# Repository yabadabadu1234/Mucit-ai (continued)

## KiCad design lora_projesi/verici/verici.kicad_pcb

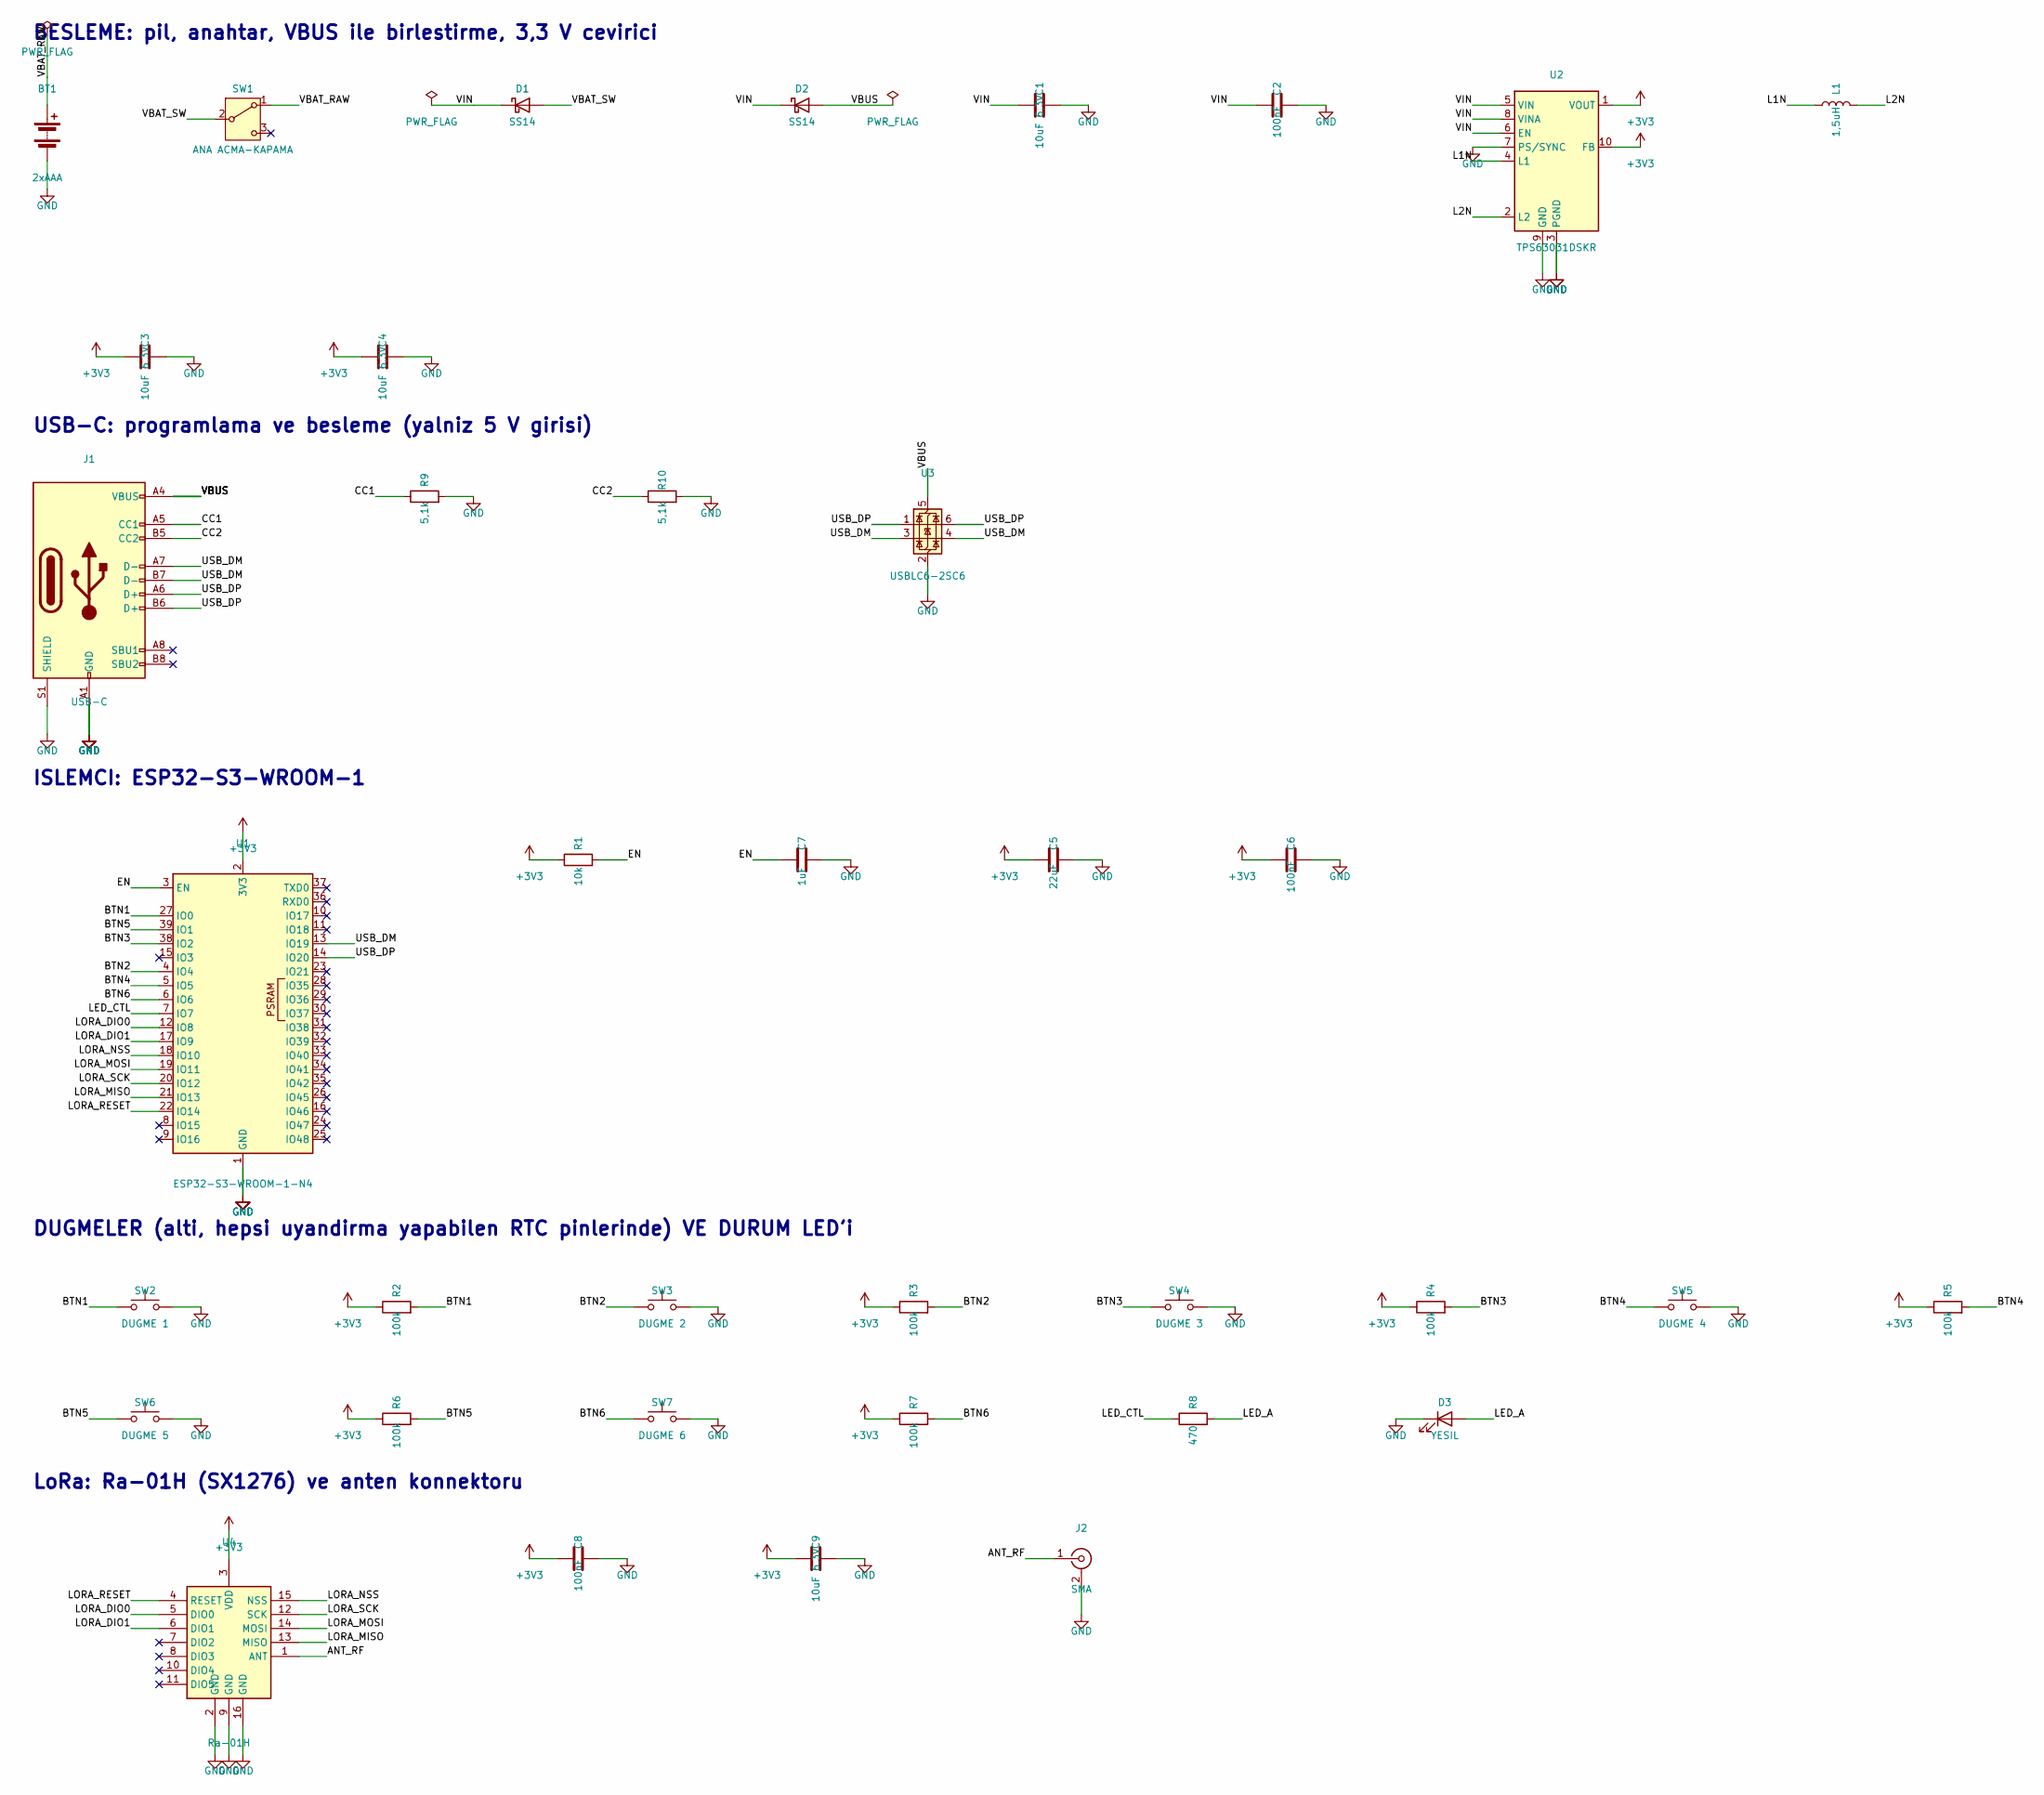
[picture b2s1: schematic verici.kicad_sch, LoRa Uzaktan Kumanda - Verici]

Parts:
BT1: 2xAAA; BatteryHolder_Keystone_2468_2xAAA; MPN Keystone 2468
C1, C3, C4, C9: 10uF 6,3V; C_0603_1608Metric
C2, C6, C8: 100nF; C_0603_1608Metric
C5: 22uF; C_0805_2012Metric
C7: 1uF; C_0603_1608Metric
D1, D2: SS14; D_SMA; MPN SS14
D3: YESIL; LED_0603_1608Metric
J1: USB-C; USB_C_Receptacle_GCT_USB4105-xx-A_16P_TopMnt_Horizontal; MPN GCT USB4105-GF-A
J2: SMA; SMA_Amphenol_132289_EdgeMount; MPN Amphenol 132289 (kenar SMA)
L1: 1,5uH; L_Cenker_CKCS3015; MPN 1,5uH 3x3mm (Coilcraft LPS3015-152 esde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
R1: 10k; R_0603_1608Metric
R2, R3, R4, R5, R6, R7: 100k; R_0603_1608Metric
R8: 470; R_0603_1608Metric
R9, R10: 5,1k; R_0603_1608Metric
SW1: ANA ACMA-KAPAMA; SW_SPDT_PCM12; MPN MSK12C02 (kayar anahtar)
SW2: DUGME 1; SW_SPST_TL3342
SW3: DUGME 2; SW_SPST_TL3342
SW4: DUGME 3; SW_SPST_TL3342
SW5: DUGME 4; SW_SPST_TL3342
SW6: DUGME 5; SW_SPST_TL3342
SW7: DUGME 6; SW_SPST_TL3342
U1: ESP32-S3-WROOM-1-N4; ESP32-S3-WROOM-1; MPN ESP32-S3-WROOM-1-N4
U2: TPS63031DSKR; WSON-10-1EP_2.5x2.5mm_P0.5mm_EP1.2x2mm; MPN TPS63031DSKR
U3: USBLC6-2SC6; SOT-23-6; MPN USBLC6-2SC6
U4: Ra-01H; MPN Ai-Thinker Ra-01H (LCSC C503593)

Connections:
+3V3: C3.1, C4.1, C5.1, C6.1, C8.1, C9.1, R1.1, R2.1, R3.1, R4.1, R5.1, R6.1, R7.1, U1.2 (3V3), U2.1 (VOUT), U2.10 (FB), U4.3 (VDD)
ANT_RF: J2.1 (In), U4.1 (ANT)
BTN1: R2.2, SW2.1, U1.27 (IO0)
BTN2: R3.2, SW3.1, U1.4 (IO4)
BTN3: R4.2, SW4.1, U1.38 (IO2)
BTN4: R5.2, SW5.1, U1.5 (IO5)
BTN5: R6.2, SW6.1, U1.39 (IO1)
BTN6: R7.2, SW7.1, U1.6 (IO6)
CC1: J1.A5 (CC1), R9.1
CC2: J1.B5 (CC2), R10.1
EN: C7.1, R1.2, U1.3 (EN)
GND: BT1.2 (-), C1.2, C2.2, C3.2, C4.2, C5.2, C6.2, C7.2, C8.2, C9.2, D3.1 (K), J1.A1 (GND), J1.A12 (GND), J1.B1 (GND), J1.B12 (GND), J1.S1 (SHIELD), J2.2 (Ext), R9.2, R10.2, SW2.2, SW3.2, SW4.2, SW5.2, SW6.2, SW7.2, U1.1 (GND), U1.40 (GND), U1.41 (GND), U2.3 (PGND), U2.7 (PS/SYNC), U2.9 (GND), U2.11 (PGND), U3.2 (GND), U4.2 (GND), U4.9 (GND), U4.16 (GND)
L1N: L1.1, U2.4 (L1)
L2N: L1.2, U2.2 (L2)
LED_A: D3.2 (A), R8.2
LED_CTL: R8.1, U1.7 (IO7)
LORA_DIO0: U1.12 (IO8), U4.5 (DIO0)
LORA_DIO1: U1.17 (IO9), U4.6 (DIO1)
LORA_MISO: U1.21 (IO13), U4.13 (MISO)
LORA_MOSI: U1.19 (IO11), U4.14 (MOSI)
LORA_NSS: U1.18 (IO10), U4.15 (NSS)
LORA_RESET: U1.22 (IO14), U4.4 (RESET)
LORA_SCK: U1.20 (IO12), U4.12 (SCK)
USB_DM: J1.A7 (D-), J1.B7 (D-), U1.13 (IO19), U3.3 (I/O2), U3.4 (I/O2)
USB_DP: J1.A6 (D+), J1.B6 (D+), U1.14 (IO20), U3.1 (I/O1), U3.6 (I/O1)
VBAT_RAW: BT1.1 (+), SW1.1 (A)
VBAT_SW: D1.2 (A), SW1.2 (B)
VBUS: D2.2 (A), J1.A4 (VBUS), J1.A9 (VBUS), J1.B4 (VBUS), J1.B9 (VBUS), U3.5 (VBUS)
VIN: C1.1, C2.1, D1.1 (K), D2.1 (K), U2.5 (VIN), U2.6 (EN), U2.8 (VINA)

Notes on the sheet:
BESLEME: pil, anahtar, VBUS ile birlestirme, 3,3 V cevirici
USB-C: programlama ve besleme (yalniz 5 V girisi)
ISLEMCI: ESP32-S3-WROOM-1
DUGMELER (alti, hepsi uyandirma yapabilen RTC pinlerinde) VE DURUM LED'i
LoRa: Ra-01H (SX1276) ve anten konnektoru

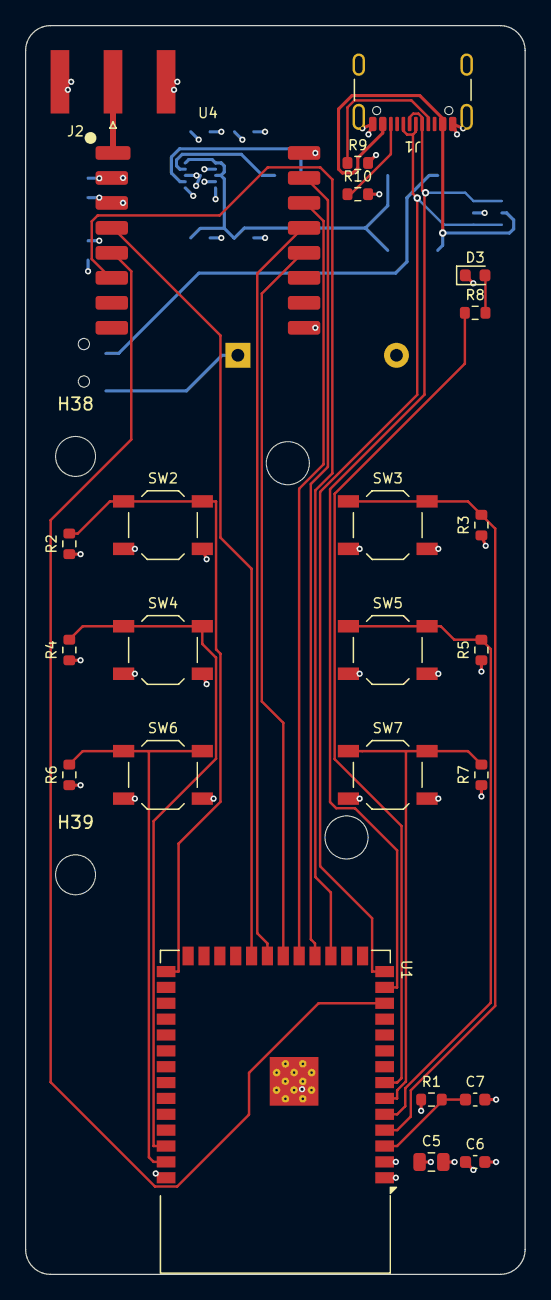
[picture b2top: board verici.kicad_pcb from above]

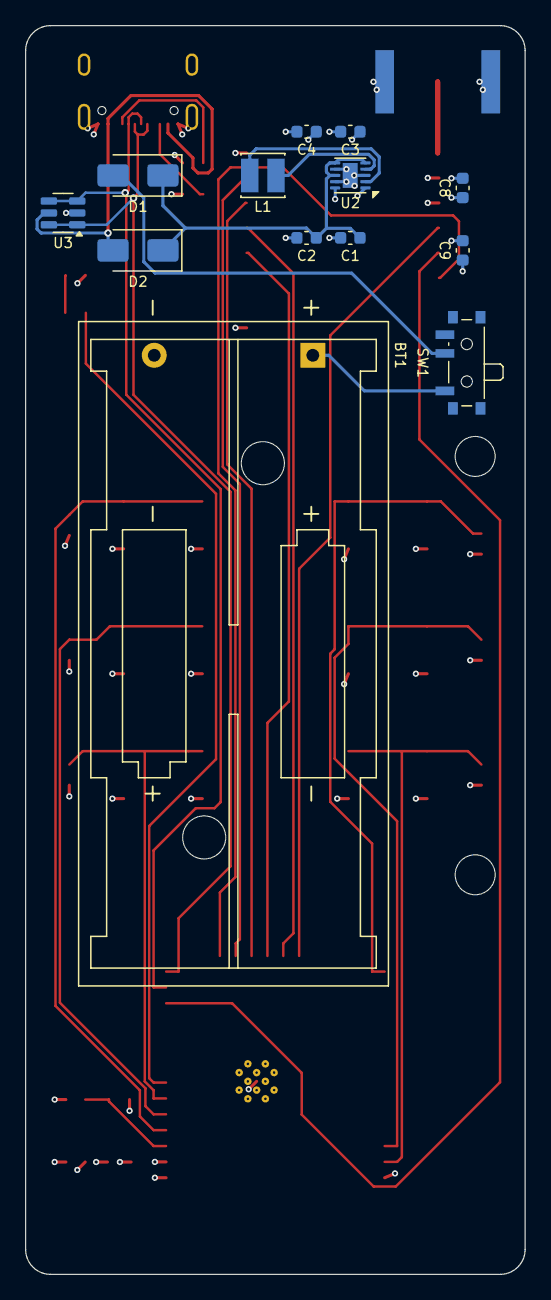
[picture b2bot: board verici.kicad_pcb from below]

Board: 4 copper layers, 40.0 x 100.0 mm, 39 parts (13 on the bottom side), 29 nets.

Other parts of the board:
H38, H39: MountingHole_3.2mm_M3
